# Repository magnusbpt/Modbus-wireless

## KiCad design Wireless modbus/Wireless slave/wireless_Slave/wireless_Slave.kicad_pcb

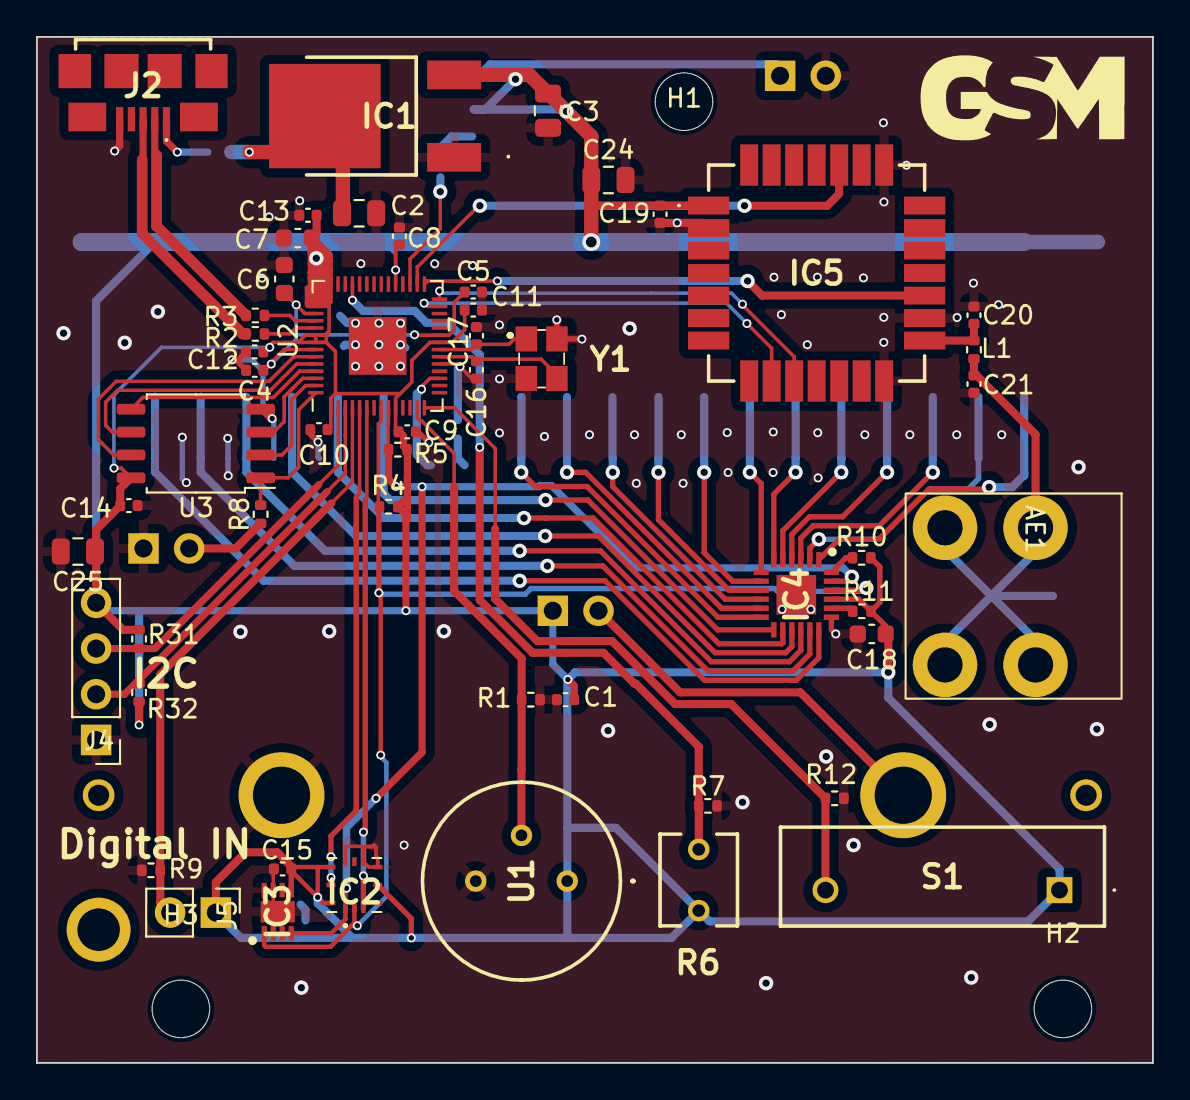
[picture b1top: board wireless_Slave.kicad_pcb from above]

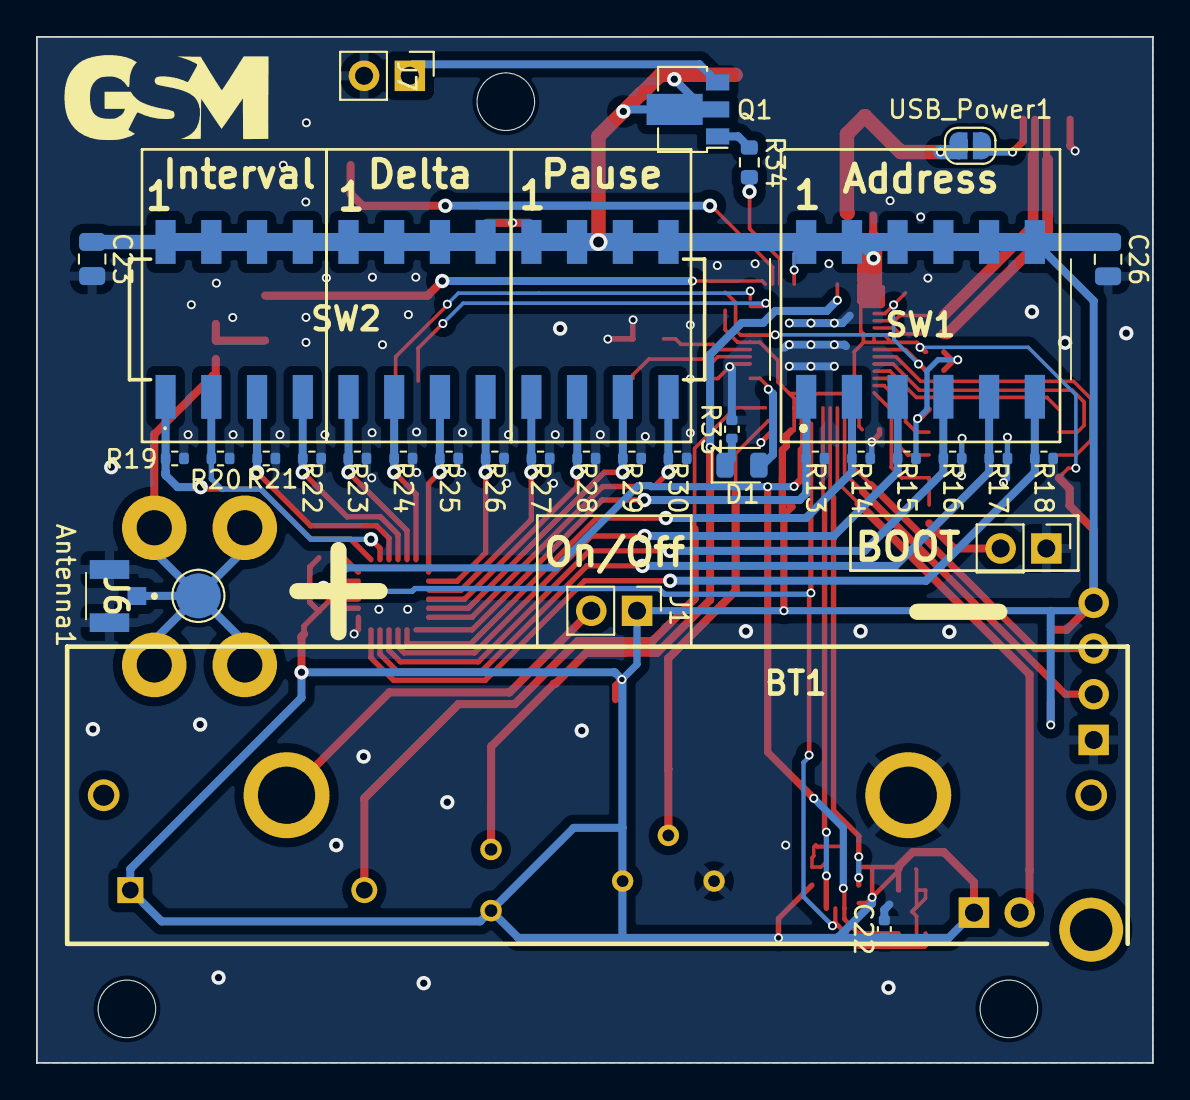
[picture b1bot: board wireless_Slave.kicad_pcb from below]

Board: 2 copper layers, 62.0 x 57.0 mm, 89 parts (34 on the bottom side), 60 nets.

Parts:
AE1: Antenna; Event_alarm_antenna
Antenna1: Antenne; TestPoint_Pad_D2.5mm
BT1: Battery_Cell; BHAA-3
C1, C4, C5, C8, C9, C10, C11, C12, C13, C14, C15, C22: 100nf; C_0402_1005Metric
C2, C3, C23, C24, C25, C26: 10uf; C_0805_2012Metric
C6, C7, C18: 1uf; C_0603_1608Metric
C16, C17: 27pf; C_0402_1005Metric
C19: 4,7uf; C_0402_1005Metric
C20, C21: NC; C_0402_1005Metric
D1: LED; LED_0805_2012Metric
H1, H2, H3: MountingHole; MountingHole_3.2mm_M3
IC1: NCP1117IDT33T4G
IC2: ZMOD4410AI1R
IC3: SHT30-DIS-B10KS; SON50P250X250X100-9N-D
IC4: ADP5587ACPZ-R7; QFN50P400X400X80-25N-D
IC5: LoRa-E5; LoRaE5
J1: ON/OFF; PinHeader_1x02_P2.54mm_Vertical
J2: 10118192-0002LF; 101181920002LF
J3: Conn_01x02; PinHeader_1x02_P2.54mm_Vertical
J4: I2C; PinHeader_1x04_P2.54mm_Vertical
J5: Digital_in; PinHeader_1x02_P2.54mm_Vertical
J6: 2337019-1; 23370191
J7: FAN; PinHeader_1x02_P2.54mm_Vertical
L1: 0Ω; R_0402_1005Metric
Q1: BCX56; SOT-89-3
R1, R4, R5, R7, R9, R10, R11, R12, R13, R14, R15, R16, R17, R18, R19, R20, R21, R22, R23, R24, R25, R26, R27, R28, R29, R30, R31, R32: 10KΩ; R_0402_1005Metric
R2, R3: 27Ω; R_0402_1005Metric
R6: R_Photo; 02LDR1
R8: 1KΩ; R_0402_1005Metric
R33: 70Ω; R_0402_1005Metric
R34: 2.4KΩ; R_0603_1608Metric
S1: 4081
SW1: SW_DIP_x06; 2196LPST
SW2: SW_DIP_x12; 21912LPST
U1: EKMB1107111
U2: RP2040; QFN-56-1EP_7x7mm_P0.4mm_EP3.2x3.2mm
U3: W25Q128JVS; SOIC-8_5.23x5.23mm_P1.27mm
USB_Power1: Jumper_2_Open; SolderJumper-2_P1.3mm_Open_RoundedPad1.0x1.5mm
Y1: 12MHz; X322512MSB4SI

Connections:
+1V1: C4.1, C5.1, C6.1, U2.23 (DVDD), U2.45 (VREG_VOUT), U2.50 (DVDD)
+3.3V: C1.1, C3.1, C7.1, C8.1, C9.1, C10.1, C11.1, C12.1, C13.1, C14.1, C15.1, C18.1, C19.1, C22.1, C23.1, C24.1, C25.1, C26.1, IC1.3 (INPUT), IC2.5 (VDD), IC2.10 (VDDH), IC2.12 (VDDIO), IC3.5 (VDD), IC4.21 (VCC), IC5.1 (VCC), J1.1, J4.4, J5.1, Q1.2 (C), R4.2, R5.2, R6.1, R10.2, R11.2, R31.2, R32.2, S1.1, SW1.B1, SW1.B2, SW1.B3, SW1.B4, SW1.B5, SW1.B6, SW2.B1, SW2.B2, SW2.B3, SW2.B4, SW2.B5, SW2.B6, SW2.B7, SW2.B8, SW2.B9, SW2.B10, SW2.B11, SW2.B12, U1.1 (VDD), U2.1 (IOVDD), U2.10 (IOVDD), U2.22 (IOVDD), U2.33 (IOVDD), U2.42 (IOVDD), U2.43 (ADC_AVDD), U2.44 (VREG_IN), U2.48 (USB_VDD), U2.49 (IOVDD), U3.8 (VCC)
/RPI2040_main/AIR_INT: IC2.3 (INT), U2.6 (GPIO4)
/RPI2040_main/AIR_RES: IC2.11 (RES_N), U2.5 (GPIO3)
/RPI2040_main/C0: IC4.9 (C0), R27.2, SW2.A9
/RPI2040_main/C1: IC4.10 (C1), R28.2, SW2.A10
/RPI2040_main/C2: IC4.11 (C2), R29.2, SW2.A11
/RPI2040_main/C3: IC4.12 (C3), R30.2, SW2.A12
/RPI2040_main/C4: IC4.13 (C4), R13.2, SW1.A1
/RPI2040_main/C5: IC4.14 (C5), R14.2, SW1.A2
/RPI2040_main/C6: IC4.15 (C6), R15.2, SW1.A3
/RPI2040_main/C7: IC4.16 (C7), R16.2, SW1.A4
/RPI2040_main/C8: IC4.17 (C8), R17.2, SW1.A5
/RPI2040_main/C9: IC4.18 (C9), R18.2, SW1.A6
/RPI2040_main/D+: J2.3, R2.1
/RPI2040_main/D-: J2.2, R3.1
/RPI2040_main/Digital_in: J5.2, R9.2, U2.4 (GPIO2)
/RPI2040_main/LUX: R6.2, R7.2, U2.39 (GPIO27_ADC1)
/RPI2040_main/LoRa_Boot: IC5.24 (PB13), U2.30 (GPIO19)
/RPI2040_main/LoRa_RXD: IC5.10 (PB6), U2.28 (GPIO17)
/RPI2040_main/LoRa_Reset: IC5.17 (RST), U2.29 (GPIO18)
/RPI2040_main/LoRa_TXD: IC5.9 (PB7), U2.27 (GPIO16)
/RPI2040_main/PIR: R1.2, U1.2 (OUT), U2.13 (GPIO10)
/RPI2040_main/QSPI_SCLK: U2.52 (QSPI_SCLK), U3.6 (CLK)
/RPI2040_main/QSPI_SD0: U2.53 (QSPI_SD0), U3.5 (DI(IO0))
/RPI2040_main/QSPI_SD1: U2.55 (QSPI_SD1), U3.2 (DO(IO1))
/RPI2040_main/QSPI_SD2: U2.54 (QSPI_SD2), U3.3 (IO2)
/RPI2040_main/QSPI_SD3: U2.51 (QSPI_SD3), U3.7 (IO3)
/RPI2040_main/QSPI_SS: R8.2, U2.56 (QSPI_SS), U3.1 (~CS)
/RPI2040_main/R0: IC4.8 (R0), R26.2, SW2.A8
/RPI2040_main/R1: IC4.7 (R1), R25.2, SW2.A7
/RPI2040_main/R2: IC4.6 (R2), R24.2, SW2.A6
/RPI2040_main/R3: IC4.5 (R3), R23.2, SW2.A5
/RPI2040_main/R4: IC4.4 (R4), R22.2, SW2.A4
/RPI2040_main/R5: IC4.3 (R5), R21.2, SW2.A3
/RPI2040_main/R6: IC4.2 (R6), R20.2, SW2.A2
/RPI2040_main/R7: IC4.1 (R7), R19.2, SW2.A1
/RPI2040_main/SCL: IC2.1 (SCL), IC3.4 (SCL), IC4.23 (SCL), R5.1, U2.9 (GPIO7)
/RPI2040_main/SCL0: J4.2, R32.1, U2.3 (GPIO1)
/RPI2040_main/SDA: IC2.2 (SDA), IC3.1 (SDA), IC4.22 (SDA), R4.1, U2.8 (GPIO6)
/RPI2040_main/SDA0: J4.3, R31.1, U2.2 (GPIO0)
/RPI2040_main/Vibration: R12.2, S1.2, U2.14 (GPIO11)
GND: BT1.2 (-), C1.2, C2.2, C3.2, C4.2, C5.2, C6.2, C7.2, C8.2, C9.2, C10.2, C11.2, C12.2, C13.2, C14.2, C15.2, C16.1, C17.1, C18.2, C19.2, C20.2, C21.2, C22.2, C23.2, C24.2, C25.2, C26.2, IC1.1 (ADJUST/GROUND), IC2.6 (VSS_1), IC2.7 (VSS_2), IC2.9 (VSS_3), IC3.2 (ADDR), IC3.7 (R), IC3.8 (VSS), IC3.9 (EP), IC4.19 (GND), IC4.25 (EP), IC5.2 (GND_1), IC5.14 (GND_2), IC5.16 (GND_3), IC5.22 (GND_4), J2.5, J3.1, J4.1, J6.2 (GND), J6.3 (GND_2), J7.2, R1.1, R7.1, R9.1, R12.1, R13.1, R14.1, R15.1, R16.1, R17.1, R18.1, R19.1, R20.1, R21.1, R22.1, R23.1, R24.1, R25.1, R26.1, R27.1, R28.1, R29.1, R30.1, R33.2, U1.3 (GND), U2.19 (TESTEN), U2.57 (GND), U3.4 (GND), Y1.2, Y1.4
unnamed: AE1.1 (A), Antenna1.1, C21.1, J6.1 (SIGNAL), L1.2
unnamed: BT1.1 (+), J1.2
unnamed: D1.2 (A), U2.17 (GPIO14)
unnamed: D1.1 (K), R33.1
unnamed: C2.1, IC1.2 (OUTPUT), USB_Power1.2 (B)
unnamed: IC4.24 (~INT), R10.1
unnamed: IC4.20 (~RST), R11.1
unnamed: C20.1, IC5.15 (RFIO), L1.1
unnamed: J3.2, R8.1
unnamed: J7.1, Q1.3 (E)
unnamed: Q1.1 (B), R34.1
unnamed: R34.2, U2.31 (GPIO20)
unnamed: R3.2, U2.46 (USB_DM)
unnamed: R2.2, U2.47 (USB_DP)
unnamed: C16.2, U2.20 (XIN), Y1.3
unnamed: C17.2, U2.21 (XOUT), Y1.1
unnamed: J2.1, USB_Power1.1 (A)

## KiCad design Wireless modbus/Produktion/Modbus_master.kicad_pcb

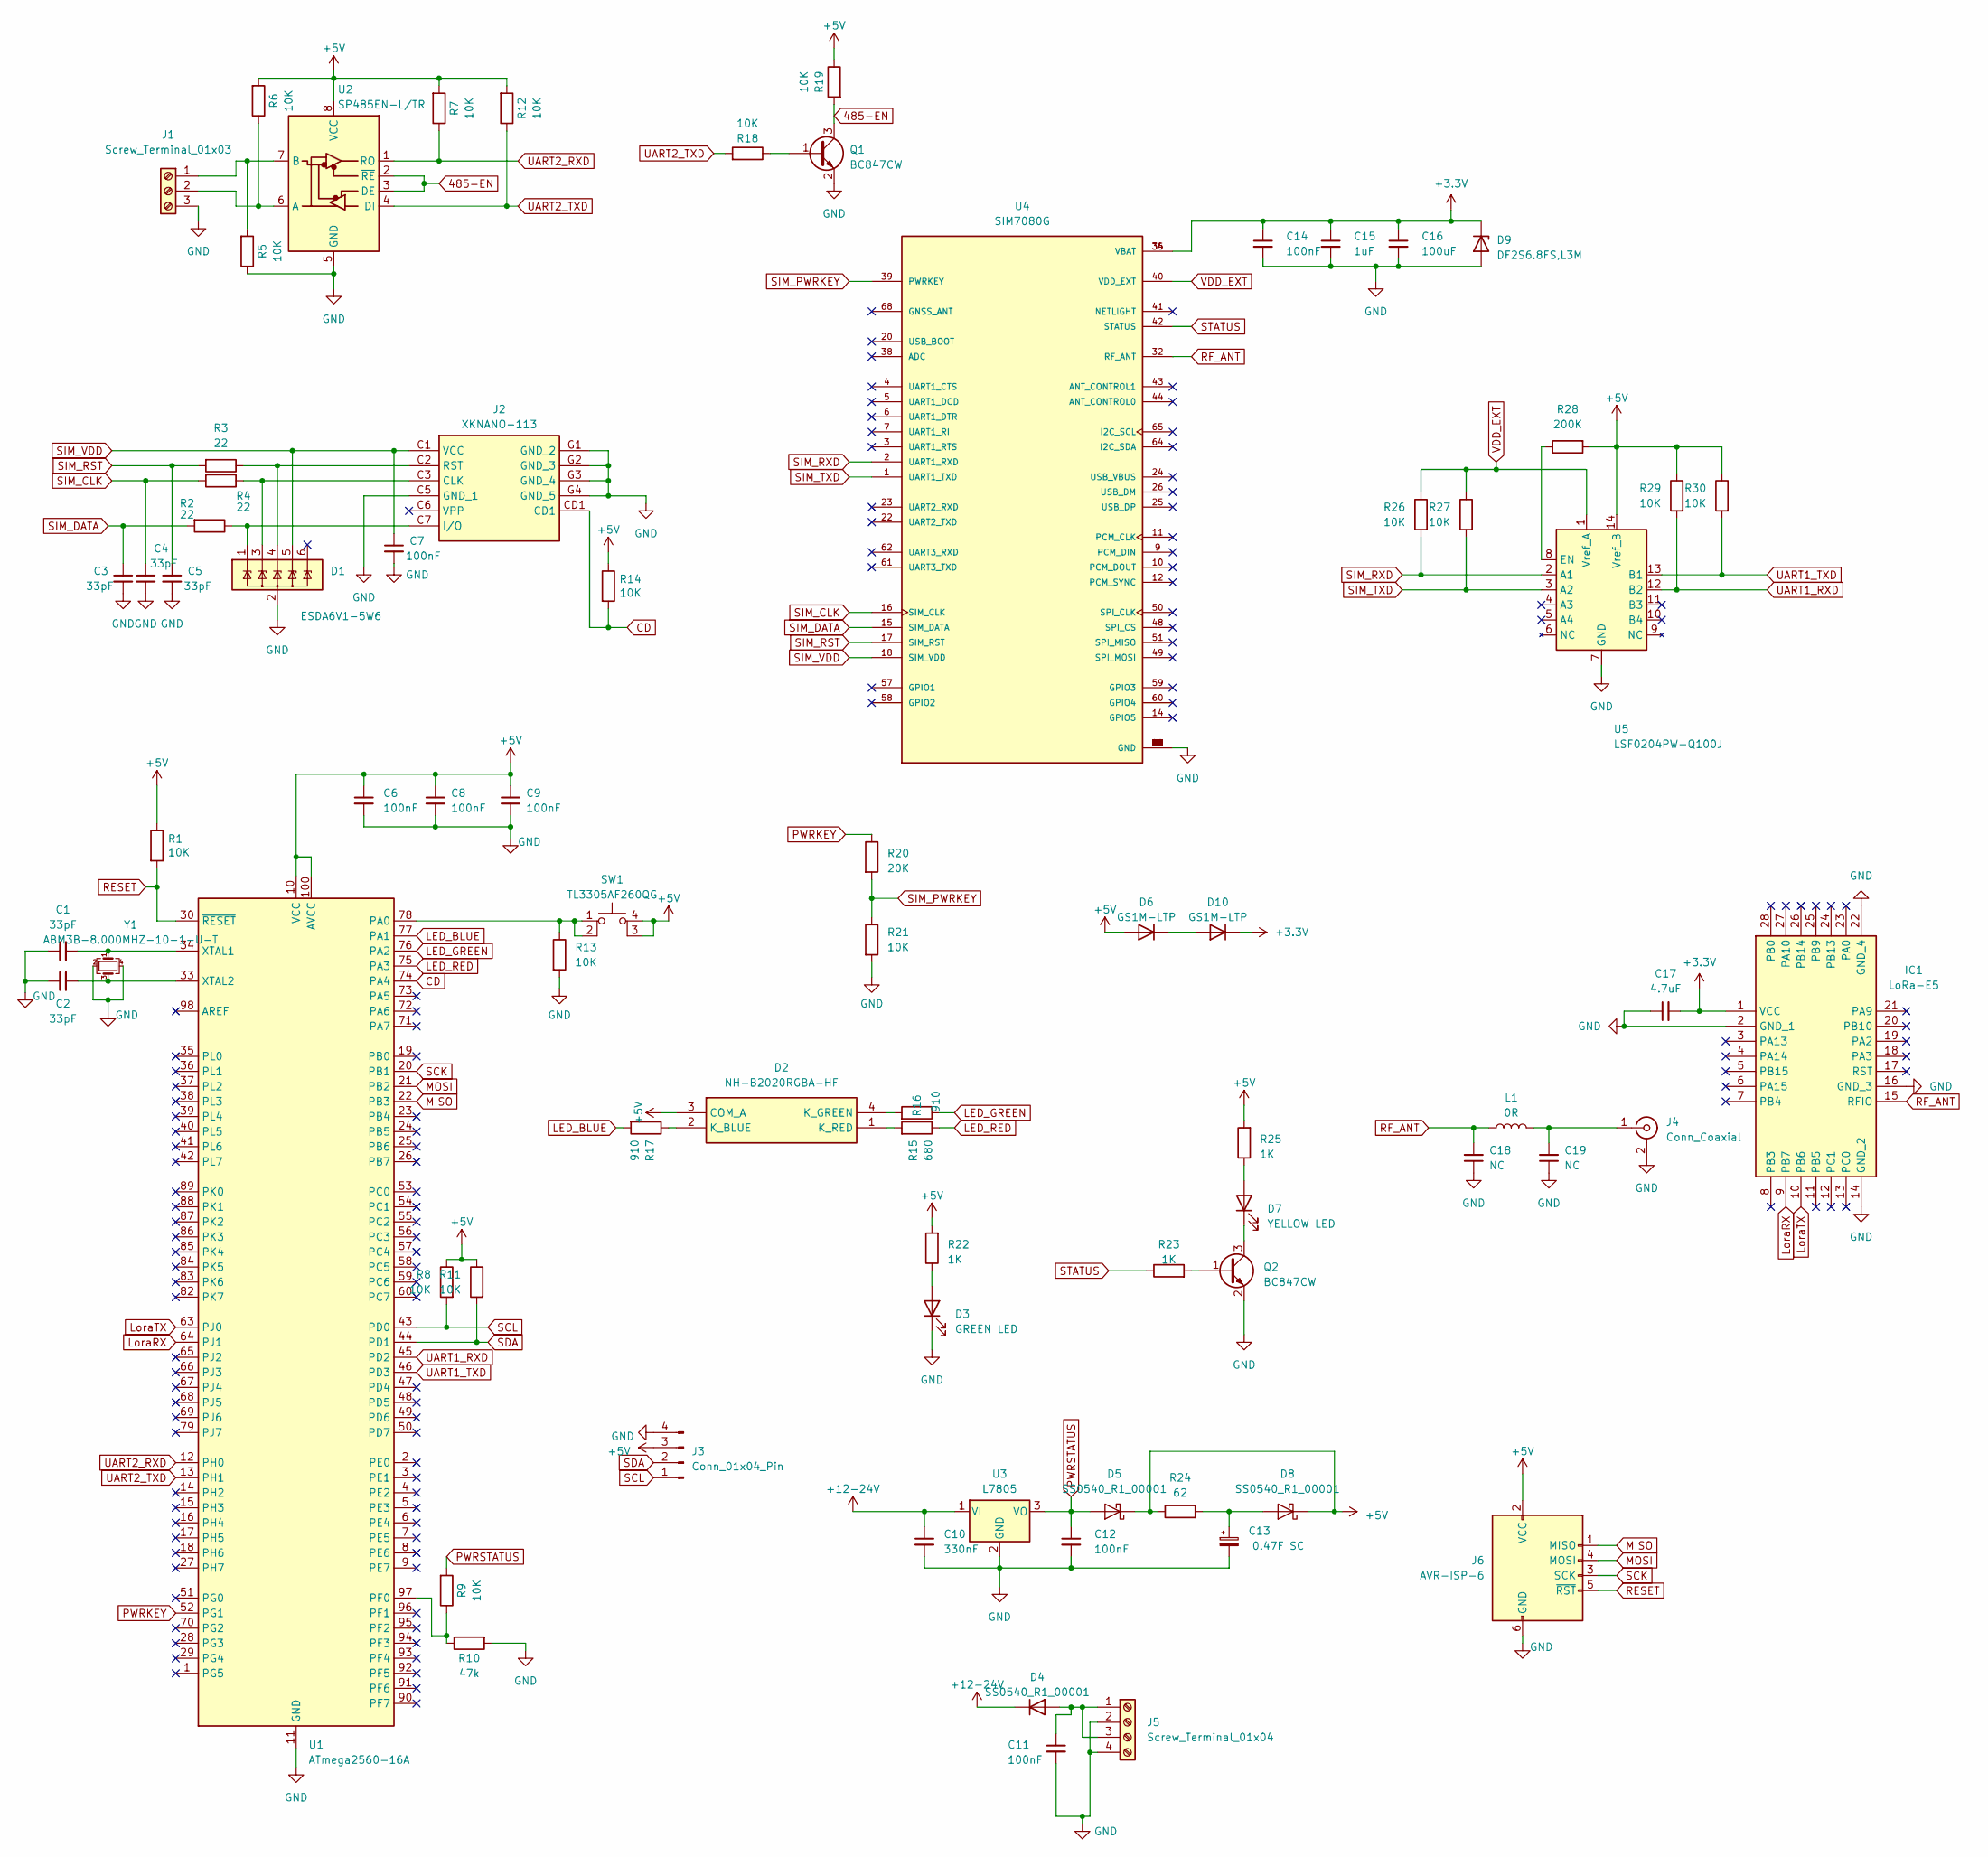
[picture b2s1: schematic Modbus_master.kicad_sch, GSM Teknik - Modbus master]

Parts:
C1, C2, C3, C4, C5: 33pF; C_0402_1005Metric; Manufacturer_Part_Number C0402C330J5GAC; Mouser Price/Stock 0,094
C6, C7, C8, C9, C11, C12, C14: 100nF; C_0402_1005Metric; Manufacturer_Part_Number C1005X7R1C104K050BC; Mouser Price/Stock 0,094
C10: 330nF; C_0805_2012Metric; Manufacturer_Part_Number CL21B334KBFNNNG; Mouser Price/Stock 0,094
C13: 0.47F SC; Radial_D6.3mm_W13.6mm_P9.00mm; Manufacturer_Part_Number SCMQ14D474PRBB0; Mouser Price/Stock 2,66
C15: 1uF; C_0402_1005Metric; Manufacturer_Part_Number GRM155R70J105KA12D; Mouser Price/Stock 0,113
C16: 100uF; C_1206_3216Metric; Manufacturer_Part_Number CL31A107MQHNNWE; Mouser Price/Stock 0,893
C17: 4.7uF; C_0402_1005Metric; Manufacturer_Part_Number GRM155R70J105KA12D; Mouser Price/Stock 0,113
C18, C19: NC; C_0402_1005Metric; Manufacturer_Part_Number GRM155R70J105KA12D; Mouser Price/Stock 0,113
D1: ESDA6V1-5W6; SOT323-6L; Manufacturer_Part_Number ESDA6V1-5W6; Mouser Price/Stock 0,545
D2: NH-B2020RGBA-HF; NHB2020RGBAHF; Manufacturer_Part_Number NH-B2020RGBA-HF; JLCPART# C2874116
D3: GREEN LED; LED_0603_1608Metric; Manufacturer_Part_Number 150060VS75000; Mouser Price/Stock 0,141
D4, D5, D8: SS0540_R1_00001; D_SOD-123; Manufacturer_Part_Number SS0540_R1_00001; Mouser Price/Stock 0,254
D6, D10: GS1M-LTP; D_SMA; Manufacturer_Part_Number GS1M-LTP; Mouser Price/Stock 0,15
D7: YELLOW LED; LED_0603_1608Metric; Manufacturer_Part_Number 150060YS75000; Mouser Price/Stock 0,141
D9: DF2S6.8FS,L3M; D_SOD-923; Manufacturer_Part_Number DF2S6.8FS,L3M; Mouser Price/Stock 0,263
IC1: LoRa-E5; LoRaE5; Manufacturer_Part_Number LoRa-E5
J1: Screw_Terminal_01x03; TerminalBlock_Phoenix_PT-1,5-3-5.0-H_1x03_P5.00mm_Horizontal; Manufacturer_Part_Number TB002-500-03BE; Mouser Price/Stock 0,686
J2: XKNANO-113; SIM8066611401A; Mouser Part Number 640-SIM8066-611401A
J3: Conn_01x04_Pin; PinHeader_1x04_P2.54mm_Vertical
J4: Conn_Coaxial; U.FL_Hirose_U.FL-R-SMT-1_Vertical; Manufacturer_Part_Number U.FL-R-SMT-1(10); Mouser Price/Stock 1,18
J5: Screw_Terminal_01x04; TerminalBlock_Phoenix_PT-1,5-4-5.0-H_1x04_P5.00mm_Horizontal; Manufacturer_Part_Number TB002-500-04BE; Mouser Price/Stock 0,902
J6: AVR-ISP-6; PinHeader_2x03_P2.54mm_Vertical; Manufacturer_Part_Number 54102-T06-00; Mouser Price/Stock 0,094
L1: 0R; R_0402_1005Metric; JLCPART# C881335
Q1, Q2: BC847CW; SOT-323_SC-70; Manufacturer_Part_Number BC847CW,115; Mouser Price/Stock 0,16
R1, R5, R6, R7, R8, R9, R11, R12, R13, R14, R18, R19, R21, R26, R27, R29, R30: 10K; R_0402_1005Metric; Manufacturer_Part_Number RC0402FR-7W10KL; Mouser Price/Stock 0,001
R2, R3, R4: 22; R_0402_1005Metric; Manufacturer_Part_Number 0402WGF220JTCE; Mouser Price/Stock 0,004
R10: 47k; R_0402_1005Metric; Manufacturer_Part_Number 0402WGF4702TCE; Mouser Price/Stock 0,004
R15: 680; R_0402_1005Metric; Manufacturer_Part_Number 0402WGF6800TCE; Mouser Price/Stock 0,004
R16, R17: 910; R_0402_1005Metric; Manufacturer_Part_Number CR0402-FX-9100GLF; Mouser Price/Stock 0,094
R20: 20K; R_0402_1005Metric; Manufacturer_Part_Number 0402WGF2002TCE; Mouser Price/Stock 0,004
R22, R23, R25: 1K; R_0402_1005Metric; Manufacturer_Part_Number 0402WGF1001TCE; Mouser Price/Stock 0,001
R24: 62; R_0805_2012Metric; Manufacturer_Part_Number ERJ-P06J620V; Mouser Price/Stock 0,122
R28: 200K; R_0402_1005Metric; Manufacturer_Part_Number 0402WGF2003TCE; Mouser Price/Stock 0,004
SW1: TL3305AF260QG; Manufacturer_Part_Number TL3305AF260QG; Mouser Price/Stock 0,197
U1: ATmega2560-16A; TQFP-100_14x14mm_P0.5mm; Manufacturer_Part_Number ATMEGA2560-16AU; Mouser Price/Stock 15,33
U2: SP485EN-L/TR; SOIC-8_3.9x4.9mm_P1.27mm; Manufacturer_Part_Number SP485EN-L/TR; Mouser Price/Stock 0,968
U3: L7805; TO-220-3_Vertical; Manufacturer_Part_Number L7805CV; Mouser Price/Stock 0,649
U4: SIM7080G; XCVR_SIM7080G; PARTREV 1.04; Mouser Price/Stock 21,79
U5: LSF0204PW-Q100J; TSSOP-14_4.4x5mm_P0.65mm; Manufacturer_Part_Number LSF0204PW-Q100J; Mouser Price/Stock 0,818
Y1: ABM3B-8.000MHZ-10-1-U-T; Oscillator_SMD_abm3b; Manufacturer_Part_Number ABM3B-8.000MHZ-10-1-U-T; Mouser Price/Stock 0,743

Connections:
485-EN: Q1.3 (C), R19.2, U2.2 (~RE), U2.3 (DE)
+3.3V: C14.1, C15.1, C16.1, C17.2, D9.1 (K), D10.1 (K), IC1.1 (VCC), U4.34 (VBAT), U4.35 (VBAT)
CD: J2.CD1, R14.2, U1.74 (PA4)
GND: C1.1, C2.1, C3.2, C4.2, C5.2, C6.2, C7.2, C8.2, C9.2, C10.2, C11.2, C12.2, C13.2, C14.2, C15.2, C16.2, C17.1, C18.1, C19.1, D1.2 (GND), D3.1 (K), D9.2 (A), IC1.2 (GND_1), IC1.14 (GND_2), IC1.16 (GND_3), IC1.22 (GND_4), J1.3, J2.C5 (GND_1), J2.G1 (GND_2), J2.G2 (GND_3), J2.G3 (GND_4), J2.G4 (GND_5), J3.4, J4.2 (Ext), J5.2, J5.4, J6.6 (GND), Q1.2 (E), Q2.2 (E), R5.1, R10.2, R13.2, R21.2, U1.11 (GND), U1.32 (GND), U1.62 (GND), U1.81 (GND), U1.99 (GND), U2.5 (GND), U3.2 (GND), U4.8 (GND), U4.13 (GND), U4.19 (GND), U4.21 (GND), U4.27 (GND), U4.30 (GND), U4.31 (GND), U4.33 (GND), U4.36 (GND), U4.37 (GND), U4.45 (GND), U4.63 (GND), U4.66 (GND), U4.67 (GND), U4.69 (GND), U4.70 (GND), U4.71 (GND), U4.72 (GND), U4.73 (GND), U4.74 (GND), U4.75 (GND), U4.76 (GND), U4.77 (GND), U5.7 (GND), Y1.2, Y1.4
LED_BLUE: R17.2, U1.77 (PA1)
LED_GREEN: R16.1, U1.76 (PA2)
LED_RED: R15.1, U1.75 (PA3)
LoraRX: IC1.9 (PB7), U1.64 (PJ1)
LoraTX: IC1.10 (PB6), U1.63 (PJ0)
MISO: J6.1 (MISO), U1.22 (PB3)
MOSI: J6.4 (MOSI), U1.21 (PB2)
unnamed: D1.1 (IO1), J2.C7 (I/O), R2.1
unnamed: D1.3 (IO2), J2.C3 (CLK), R4.1
unnamed: D1.4 (IO3), J2.C2 (RST), R3.1
unnamed: D2.2 (K_BLUE), R17.1
unnamed: D2.4 (K_GREEN), R16.2
unnamed: D2.1 (K_RED), R15.2
unnamed: D3.2 (A), R22.1
unnamed: C11.1, D4.2 (A), J5.1, J5.3
unnamed: D7.2 (A), R25.1
unnamed: D7.1 (K), Q2.3 (C)
unnamed: C13.1, D8.2 (A), R24.2
unnamed: D6.1 (K), D10.2 (A)
unnamed: J1.1, R5.2, U2.7 (B)
unnamed: J1.2, R6.1, U2.6 (A)
unnamed: C19.2, J4.1 (In), L1.2
unnamed: Q1.1 (B), R18.1
unnamed: Q2.1 (B), R23.2
unnamed: R13.1, SW1.1, SW1.2, U1.78 (PA0)
unnamed: R9.1, R10.1, U1.97 (PF0)
unnamed: C1.2, U1.34 (XTAL1), Y1.1
unnamed: C2.2, U1.33 (XTAL2), Y1.3
unnamed: R28.1, U5.8 (EN)
PWRKEY: R20.1, U1.52 (PG1)
PWRSTATUS: C12.1, D5.2 (A), R9.2, U3.3 (VO)
RESET: J6.5 (~RST), R1.2, U1.30 (~RESET)
RF_ANT: C18.2, IC1.15 (RFIO), L1.1, U4.32 (RF_ANT)
SCK: J6.3 (SCK), U1.20 (PB1)
SCL: J3.1, R8.2, U1.43 (PD0)
SDA: J3.2, R11.2, U1.44 (PD1)
SIM_CLK: C4.1, R4.2, U4.16 (SIM_CLK)
SIM_DATA: C3.1, R2.2, U4.15 (SIM_DATA)
SIM_PWRKEY: R20.2, R21.1, U4.39 (PWRKEY)
SIM_RST: C5.1, R3.2, U4.17 (SIM_RST)
SIM_RXD: R26.2, U4.2 (UART1_RXD), U5.2 (A1)
SIM_TXD: R27.2, U4.1 (UART1_TXD), U5.3 (A2)
SIM_VDD: C7.1, D1.5 (IO4), J2.C1 (VCC), U4.18 (SIM_VDD)
STATUS: R23.1, U4.42 (STATUS)
UART1_RXD: R29.2, U1.45 (PD2), U5.12 (B2)
UART1_TXD: R30.2, U1.46 (PD3), U5.13 (B1)
UART2_RXD: R7.1, U1.12 (PH0), U2.1 (RO)
UART2_TXD: R12.1, R18.2, U1.13 (PH1), U2.4 (DI)
VCC_5: C6.1, C8.1, C9.1, D2.3 (COM_A), D5.1 (K), D6.2 (A), D8.1 (K), J3.3, J6.2 (VCC), R1.1, R6.2, R7.2, R8.1, R11.1, R12.2, R14.1, R19.1, R22.2, R24.1, R25.2, R28.2, R29.1, R30.1, SW1.3, SW1.4, U1.10 (VCC), U1.31 (VCC), U1.61 (VCC), U1.80 (VCC), U1.100 (AVCC), U2.8 (VCC), U5.14 (Vref_B)
VCC_12-24: C10.1, D4.1 (K), U3.1 (VI)
VDD_EXT: R26.1, R27.1, U4.40 (VDD_EXT), U5.1 (Vref_A)

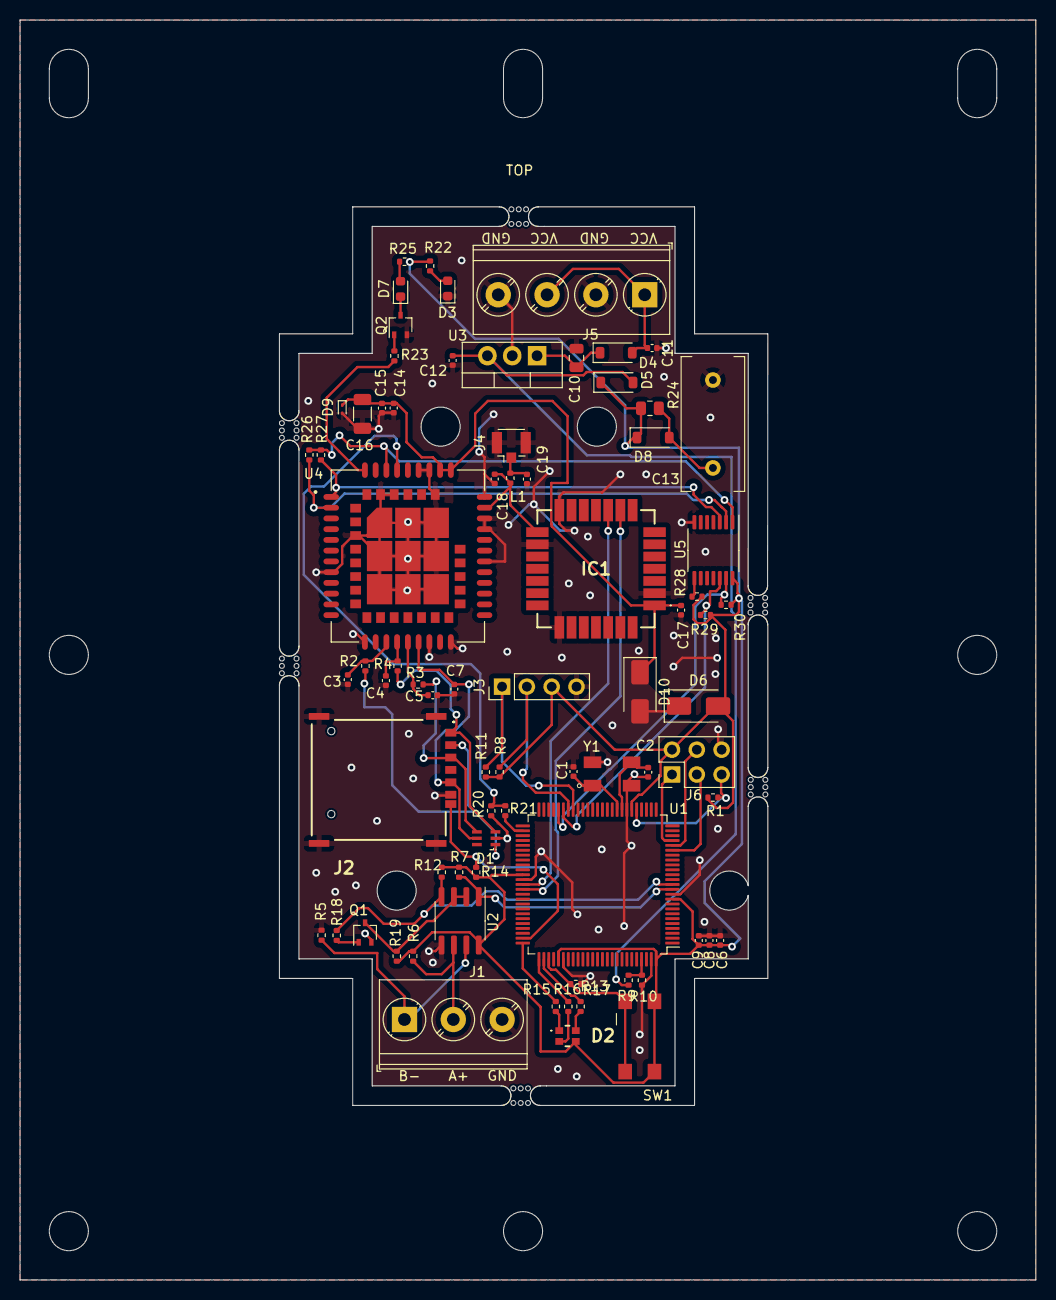
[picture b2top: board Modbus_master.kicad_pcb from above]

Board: 2 copper layers, 104.0 x 129.0 mm, 82 parts (0 on the bottom side), 55 nets.

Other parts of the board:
mouse-bite-2mm-slot, mouse-bite-2mm-slot#2, mouse-bite-2mm-slot#3, mouse-bite-2mm-slot#4, mouse-bite-2mm-slot#5, mouse-bite-2mm-slot#6: VAL**; mouse-bite-2mm-slot

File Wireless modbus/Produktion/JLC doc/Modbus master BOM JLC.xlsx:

Comment | Designator | Footprint | JLCPCB Part #
33pF | C1-5 | Capacitor_SMD:C_0402_1005Metric | C526997
100nF | C6-9, C11, C12, C14 | Capacitor_SMD:C_0402_1005Metric | C56392
330nF | C10 | Capacitor_SMD:C_0805_2012Metric | C161258
1uF | C15 | Capacitor_SMD:C_0402_1005Metric | C326568
100uF | C16 | Capacitor_SMD:C_1206_3216Metric | C76661
4.7uF | C17 | Capacitor_SMD:C_0402_1005Metric | C2858031
ESDA6V1-5W6 | D1 | SELF_MADE:SOT323-6L | C87908
NH-B2020RGBA-HF | D2 | NHB2020RGBAHF | C2874116
GREEN LED | D3 | LED_SMD:LED_0603_1608Metric | C965805
SS0540_R1_00001 | D4, D5, D8 | Diode_SMD:D_SOD-123 | C282388
GS1M-LTP | D6 | Diode_SMD:D_SMA | C435833
YELLOW LED | D7 | LED_SMD:LED_0603_1608Metric | C965802
DF2S6.8FS,L3M | D9 | Diode_SMD:D_SOD-923 | C1972978
SIM8066-6-1-14-01-A | J2 | SIM8066611401A:SIM8066611401A | C381071
Conn_Coaxial | J4 | Connector_Coaxial:U.FL_Hirose_U.FL-R-SMT-1_Vertical | C434808
0R | L1 | Resistor_SMD:R_0402_1005Metric | C881335
BC847CW | Q1, Q2 | Package_TO_SOT_SMD:SOT-323_SC-70 | C75567
10K | R1, R5-9, R11-14, R18, R19, R21, R26, R27, R29, R30 | Resistor_SMD:R_0402_1005Metric | C25744
22.0 | R2-4 | Resistor_SMD:R_0402_1005Metric | C25092
47k | R10 | Resistor_SMD:R_0402_1005Metric | C25792
680.0 | R15 | Resistor_SMD:R_0402_1005Metric | C25113
910.0 | R16, R17 | Resistor_SMD:R_0402_1005Metric | C44933
20K | R20 | Resistor_SMD:R_0402_1005Metric | C25765
1K | R22, R23, R25 | Resistor_SMD:R_0402_1005Metric | C11702
62.0 | R24 | Resistor_SMD:R_0805_2012Metric | C560547
200K | R28 | Resistor_SMD:R_0402_1005Metric | C25764
TL3305AF260QG | SW1 | SELF_MADE:TL3305AF260QG | C2886902
ATmega2560-16A | U1 | Package_QFP:TQFP-100_14x14mm_P0.5mm | C22460
SP485EN-L/TR | U2 | Package_SO:SOIC-8_3.9x4.9mm_P1.27mm | C6855
SIM7080G | U4 | SIM7080G:XCVR_SIM7080G | C2943992
LSF0204PW-Q100J | U5 | Package_SO:TSSOP-14_4.4x5mm_P0.65mm | C202288
ABM3B-8.000MHZ-10-1-U-T | Y1 | SELF_MADE:Oscillator_SMD_abm3b | C276420

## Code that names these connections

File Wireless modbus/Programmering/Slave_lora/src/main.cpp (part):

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#define i2c_int Wire1

// Define pins
#define Digital_in 2
#define AIR_RES 3
#define AIR_INT 4
#define pirSensor 10
#define Vib_Sensor 11
#define LED 14
#define LoRa_RES 18
#define LoRa_BOOT 19
#define FAN 20
#define ADC1_LUX 27
#define ADC2_DB 28
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
  // Set pins
  pinMode(pirSensor, INPUT);
  pinMode(Digital_in, INPUT);
  pinMode(LoRa_RES, OUTPUT);
  pinMode(LoRa_BOOT, OUTPUT);
  pinMode(LED, OUTPUT);

  digitalWrite(LoRa_RES, HIGH);
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
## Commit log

2023-09-08 Tilføjet modbus master
2023-09-08 Ændring
2023-09-08 slave oprette
2023-09-08 ændringer
2023-09-14 reverse
2023-09-14 Tidsplan
2023-09-14 Slave
2023-09-19 Tilføj programmering
2023-09-20 ny tidsplan
2023-10-03 Ændring i print
2023-10-19 wup wup
2023-10-31 Tilføj kicad ting
2023-11-01 ændrng
2023-11-01 dodo
2023-11-07 wupwup
2023-11-07 jaaaaaaaaaaaaa
2023-11-08 test
2023-11-08 TJEK
2023-11-17 håhå
2023-11-30 siejwi
